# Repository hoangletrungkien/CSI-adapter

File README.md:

# FRAMOS CSI Adapter (Rev 1.1.2)

An adapter board converting **FRAMOS Sensor Adapter (FSA)** interface to a **30-pin CSI Interposer (I-PEX)** connector, supporting **4-lane MIPI CSI-2**, integrated camera power supplies, and I2C logic level translation.

---

## 3D Preview

| Top View | Bottom View |
| :---: | :---: |
|  |  |

---

## Key Features

- **Interfaces:**
  - **FSA Interface (`J1`):** Hirose `DF40C-60DS-0.4V(51)` (60-pin, 0.4 mm pitch).
  - **CSI Interposer (`J2`):** `MSAK24025P30` / compatible with `STE-I-PEX-20455-030E-12` (30-pin, matching cable `KAB-I-PEX-20453-030T-0500-1:1-ROUND`).
- **High-Speed Interface:** Supports **4-lane MIPI CSI-2** (`CSI_CLK` + `CSI_D0..D3`) routed for **100 Ω differential impedance**.
- **On-board Camera Power (from `5V0_SYS`):**
  - **3V8 Rail (`U2`):** `AP62301Z6-7` Buck Converter (2.2 µH / 1.6 A inductor).
  - **1V8 Rail (`U3`):** `AP62301Z6-7` Buck Converter (2.2 µH / 1.6 A inductor).
- **I2C Level Translation (`U1`):** `NTS0102` bidirectional translator (`1V8 <-> 3V3`) with `0 Ω` bypass resistor options (`R16`, `R17` DNP) for direct 1.8 V I2C operation.
- **Extras:** `3V8_CAM` power indicator LED (`D1`), 4× mounting holes (`MP1–MP4`), and full test point access (`TP1–TP21`).

---

## Hardware Specifications

- **EDA Tool:** KiCad 10
- **Layer Stackup:** 4 Layers (`Signal / GND / Power / Signal`)
- **Impedance Control:** 100 Ω Differential (MIPI CSI-2 lanes)
- **Mounting Holes:** 4× M2 (`2.2 mm` drill, `4.5 mm` pad)

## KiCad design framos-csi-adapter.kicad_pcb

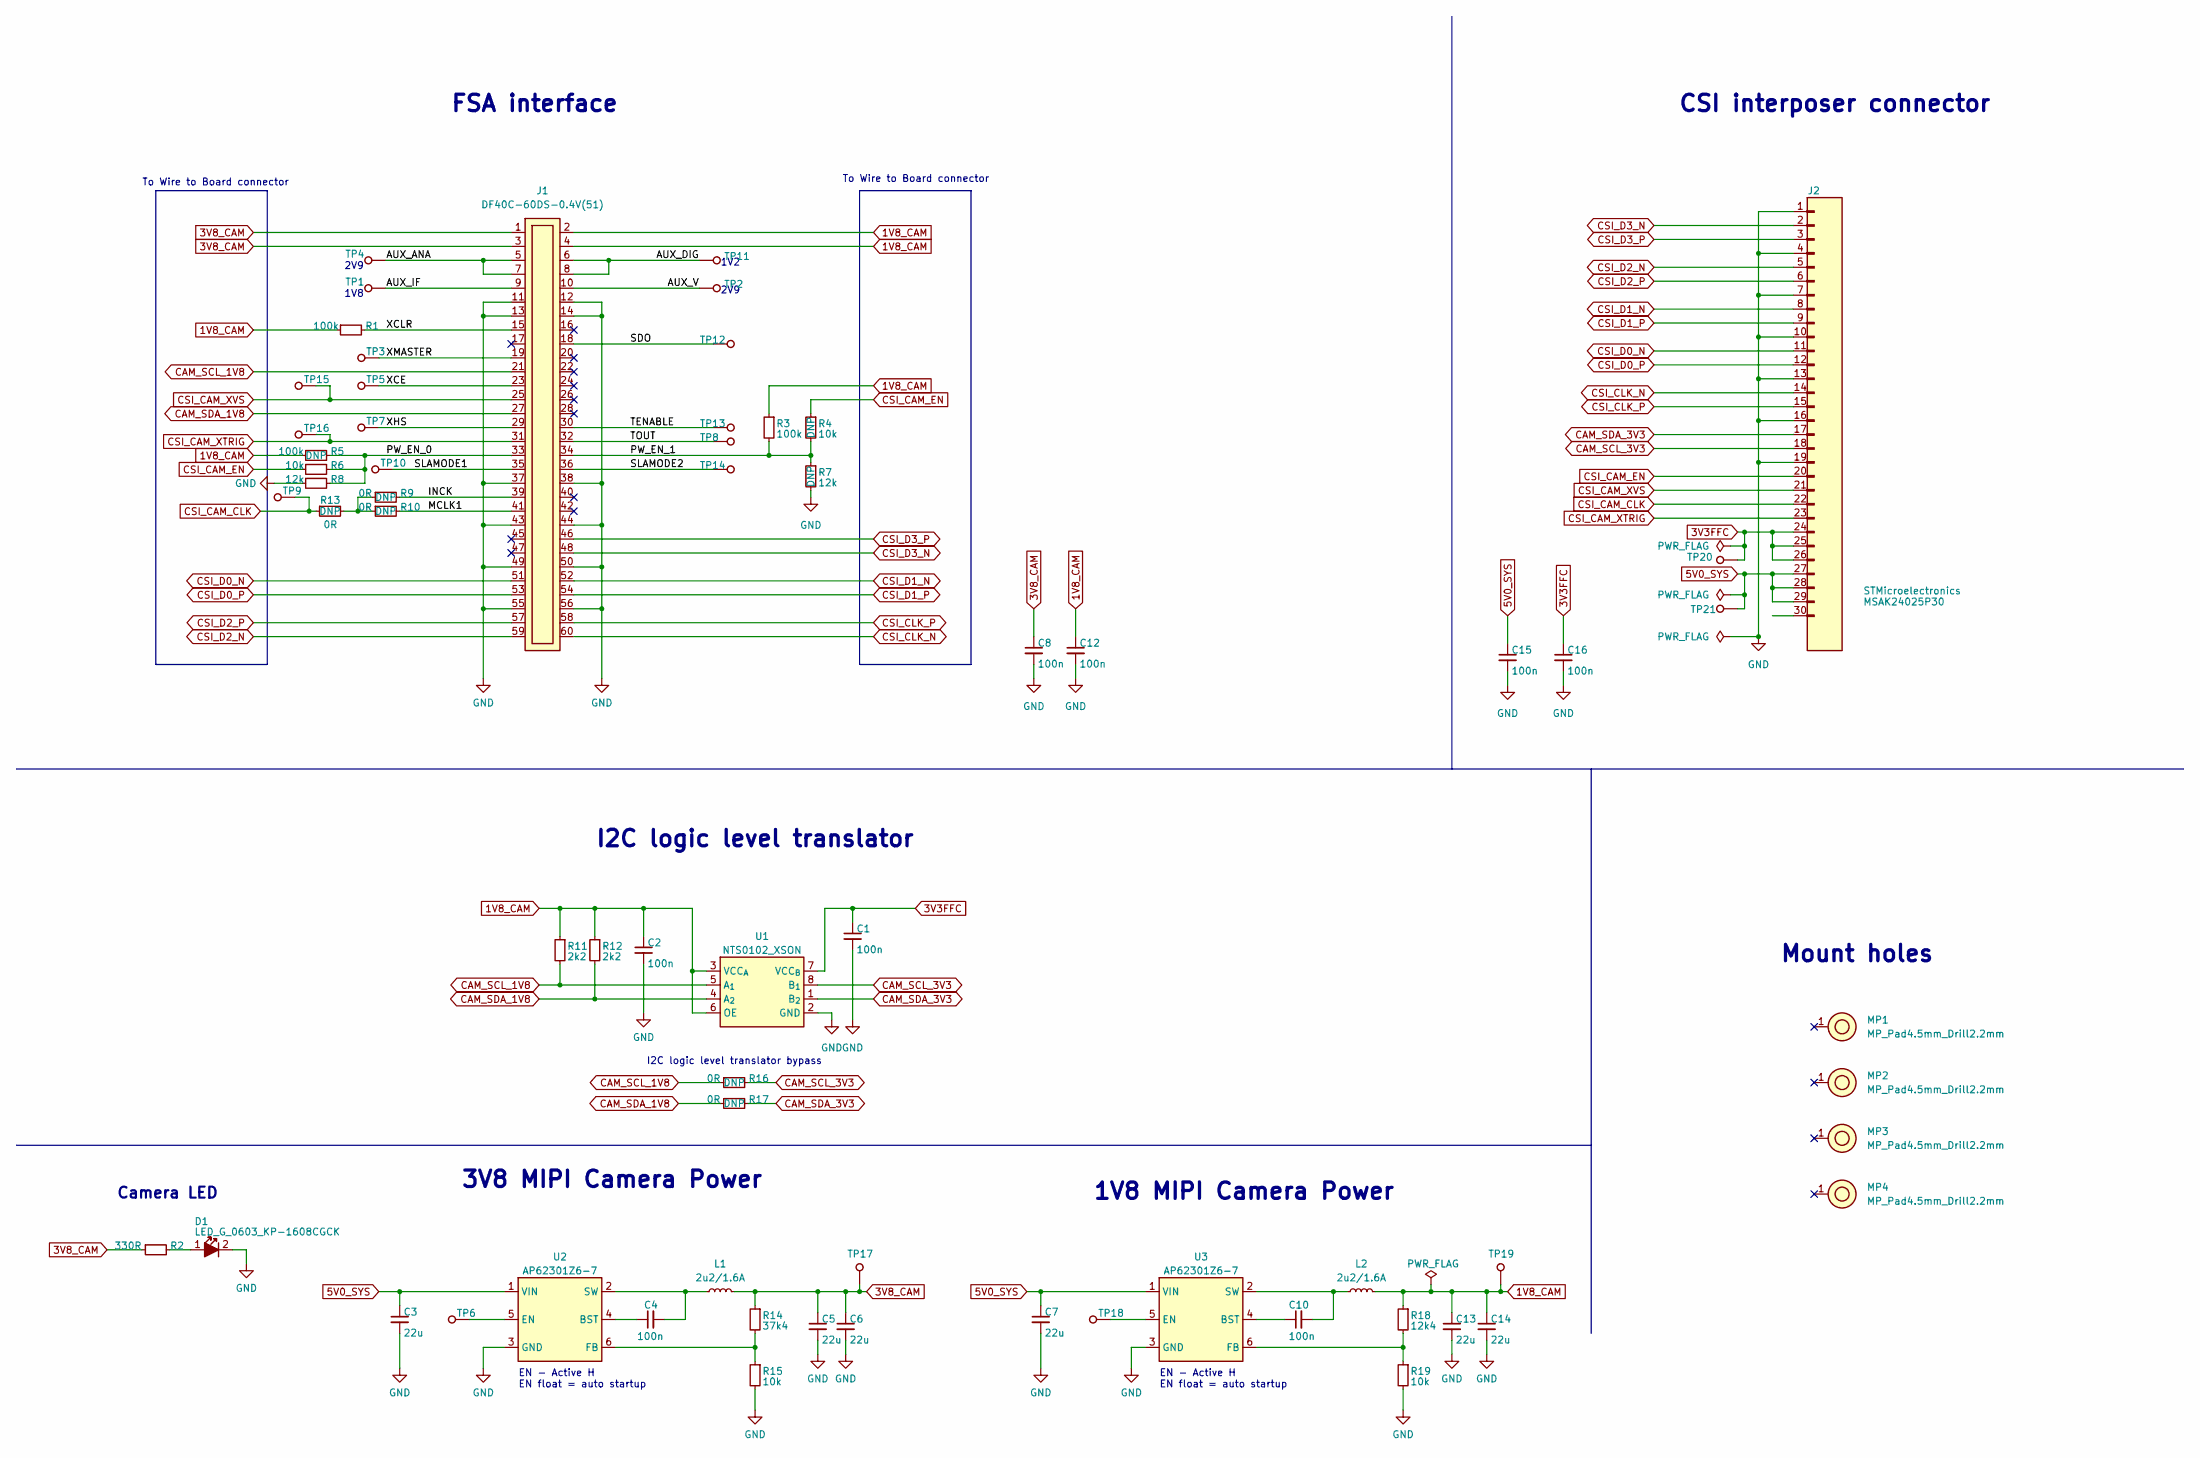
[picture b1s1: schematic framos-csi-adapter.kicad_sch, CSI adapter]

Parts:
C1, C2, C4, C8, C10, C12, C15, C16: C_100n_0402; C_0402_1005Metric; Voltage 50V; MPN GRM155R61H104KE14D
C3, C5, C6, C7, C13, C14: C_22u_0603; C_0603_1608Metric; MPN GRM188R60J226MEA0D
D1: LED_G_0603_KP-1608CGCK; LED_0603_1608Metric_G; MPN KP-1608CGCK
J1: Socket_Hirose_DF40_2x30_DF40C-60DS-0.4V; Conn_Socket_Hirose_DF40_2x30_DF40C-60DS-0.4V; MPN DF40C-60DS-0.4V(51)
J2: Conn_STM_MSAK24025P30; MPN MSAK24025P30
L1, L2: L_2u2_1.6A_1008; L_1008_2520Metric; MPN 74479887222C
MP1, MP2, MP3, MP4: MP_Pad4.5mm_Drill2.2mm
R1, R3, R5: R_100k_0402; R_0402_1005Metric; Tolerance 1%; MPN CR0402-FX-1003GLF
R2: R_330R_0402; R_0402_1005Metric; Tolerance 1%; MPN CR0402-FX-3300GLF
R4, R6, R15, R19: R_10k_0402; R_0402_1005Metric; Tolerance 1%; MPN CR0402-FX-1002GLF
R7, R8: R_12k_0402; R_0402_1005Metric; Tolerance 1%; MPN CR0402-FX-1202GLF
R9, R10, R13, R16, R17: R_0R_0402; R_0402_1005Metric; MPN ERJ2GE0R00X
R11, R12: R_2k2_0402; R_0402_1005Metric; Tolerance 1%; MPN CR0402-FX-2201GLF
R14: R_37k4_0402; R_0402_1005Metric; Tolerance 1%; MPN CR0402-FX-3742GLF
R18: R_12k4_0402; R_0402_1005Metric; Tolerance 1%; MPN CR0402-FX-1242GLF
TP1, TP2, TP3, TP4, TP5, TP6, TP7, TP8, TP9, TP10, TP11, TP12, TP13, TP14, TP15, TP16, TP17, TP19, TP20, TP21: TP_0.75mm_SMD; TP_SMD_0.75mm
TP18: TP_1mm_SMD; TP_SMD_0.75mm
U1: NTS0102_XSON; XSON-8_1x1.95mm_P0.5mm; MPN NTS0102GT
U2, U3: AP62301Z6-7; SOT-563; MPN AP62301Z6-7

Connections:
1V8_CAM: C2.1, C12.1, C13.1, C14.1, J1.2, J1.4, L2.2, R1.1, R3.1, R5.1, R11.1, R12.1, R18.1, TP19.1 (1_1), U1.3 (VCC_{A}), U1.6 (OE)
3V3FFC: C1.1, C16.1, J2.24, J2.25, J2.26, TP20.1 (1_1), U1.7 (VCC_{B})
3V8_CAM: C5.1, C6.1, C8.1, J1.1, J1.3, L1.2, R2.1, R14.1, TP17.1 (1_1)
5V0_SYS: C3.1, C7.1, C15.1, J2.27, J2.28, J2.29, TP21.1 (1_1), U2.1 (VIN), U3.1 (VIN)
/AUX_ANA: J1.5, J1.7, TP4.1 (1_1)
/AUX_DIG: J1.6, J1.8, TP11.1 (1_1)
/AUX_IF: J1.9, TP1.1 (1_1)
/AUX_V: J1.10, TP2.1 (1_1)
/INCK: J1.39, R9.2
/MCLK1: J1.41, R10.2
/PW_EN_0: J1.33, R5.2, R6.2, R8.2
/PW_EN_1: J1.34, R3.2, R4.2, R7.1
/SDO: J1.18, TP12.1 (1_1)
/SLAMODE1: J1.35, TP10.1 (1_1)
/SLAMODE2: J1.36, TP14.1 (1_1)
/TENABLE: J1.30, TP13.1 (1_1)
/TOUT: J1.32, TP8.1 (1_1)
/XCE: J1.23, TP5.1 (1_1)
/XCLR: J1.15, R1.2
/XHS: J1.29, TP7.1 (1_1)
/XMASTER: J1.19, TP3.1 (1_1)
CAM_SCL_1V8: J1.21, R11.2, R16.1, U1.5 (A_{1})
CAM_SCL_3V3: J2.18, R16.2, U1.8 (B_{1})
CAM_SDA_1V8: J1.27, R12.2, R17.1, U1.4 (A_{2})
CAM_SDA_3V3: J2.17, R17.2, U1.1 (B_{2})
CSI_CAM_CLK: J2.22, R13.1, TP9.1 (1_1)
CSI_CAM_EN: J2.20, R4.1, R6.1
CSI_CAM_XTRIG: J1.31, J2.23, TP16.1 (1_1)
CSI_CAM_XVS: J1.25, J2.21, TP15.1 (1_1)
CSI_CLK_N: J1.60, J2.14
CSI_CLK_P: J1.58, J2.15
CSI_D0_N: J1.51, J2.11
CSI_D0_P: J1.53, J2.12
CSI_D1_N: J1.52, J2.8
CSI_D1_P: J1.54, J2.9
CSI_D2_N: J1.59, J2.5
CSI_D2_P: J1.57, J2.6
CSI_D3_N: J1.48, J2.2
CSI_D3_P: J1.46, J2.3
GND: C1.2, C2.2, C3.2, C5.2, C6.2, C7.2, C8.2, C12.2, C13.2, C14.2, C15.2, C16.2, D1.2, J1.11, J1.12, J1.13, J1.14, J1.37, J1.38, J1.43, J1.44, J1.49, J1.50, J1.55, J1.56, J2.1, J2.4, J2.7, J2.10, J2.13, J2.16, J2.19, R7.2, R8.1, R15.2, R19.2, U1.2 (GND), U2.3 (GND), U3.3 (GND)
unnamed: D1.1, R2.2
unnamed: R9.1, R10.1, R13.2
unnamed: C4.1, U2.4 (BST)
unnamed: TP6.1 (1_1), U2.5 (EN)
unnamed: R14.2, R15.1, U2.6 (FB)
unnamed: C4.2, L1.1, U2.2 (SW)
unnamed: C10.1, U3.4 (BST)
unnamed: TP18.1 (1_1), U3.5 (EN)
unnamed: R18.2, R19.1, U3.6 (FB)
unnamed: C10.2, L2.1, U3.2 (SW)

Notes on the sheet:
To Wire to Board connector
EN - Active H EN float = auto startup
FSA interface
1V8 MIPI Camera Power
1V8
Mount holes
CSI interposer connector
I2C logic level translator
1V2
2V9
Camera LED
I2C logic level translator bypass
3V8 MIPI Camera Power

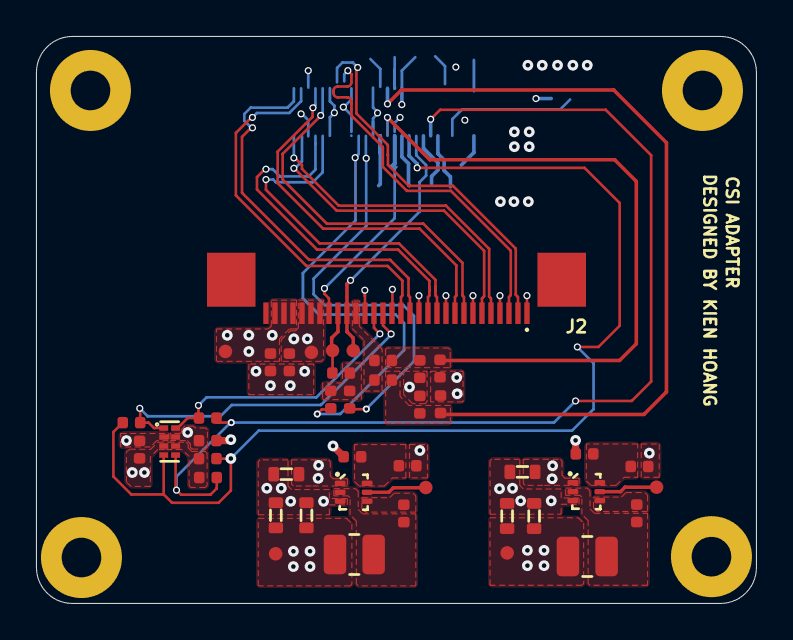
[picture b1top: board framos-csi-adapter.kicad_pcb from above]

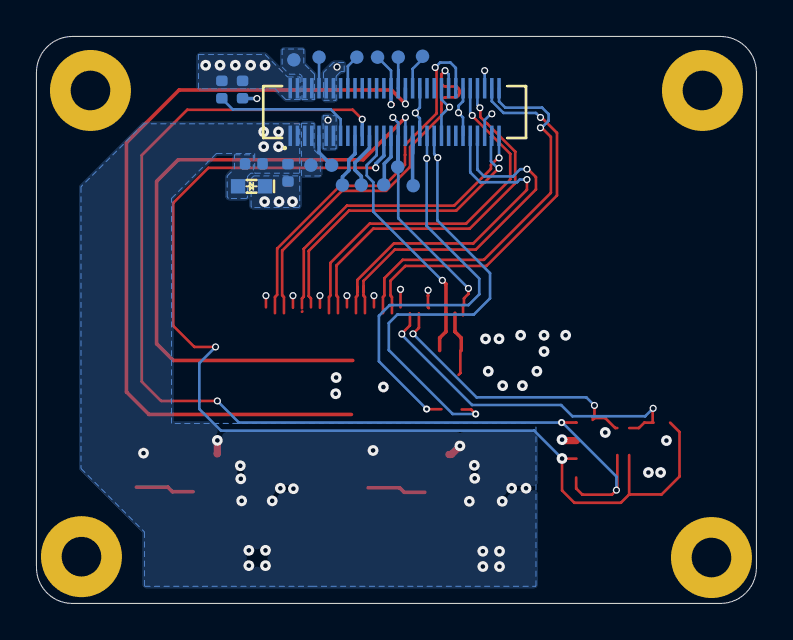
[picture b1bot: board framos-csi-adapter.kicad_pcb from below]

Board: 4 copper layers, 40.0 x 31.5 mm, 66 parts (19 on the bottom side), 50 nets.

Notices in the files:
parts and their libraries:
License: Apache-2.0
